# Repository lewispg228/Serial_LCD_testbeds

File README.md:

# Serial_LCD_testbeds
This repo will house testbeds for the new Serial LCDs (both versions: 16x2, 20x4)

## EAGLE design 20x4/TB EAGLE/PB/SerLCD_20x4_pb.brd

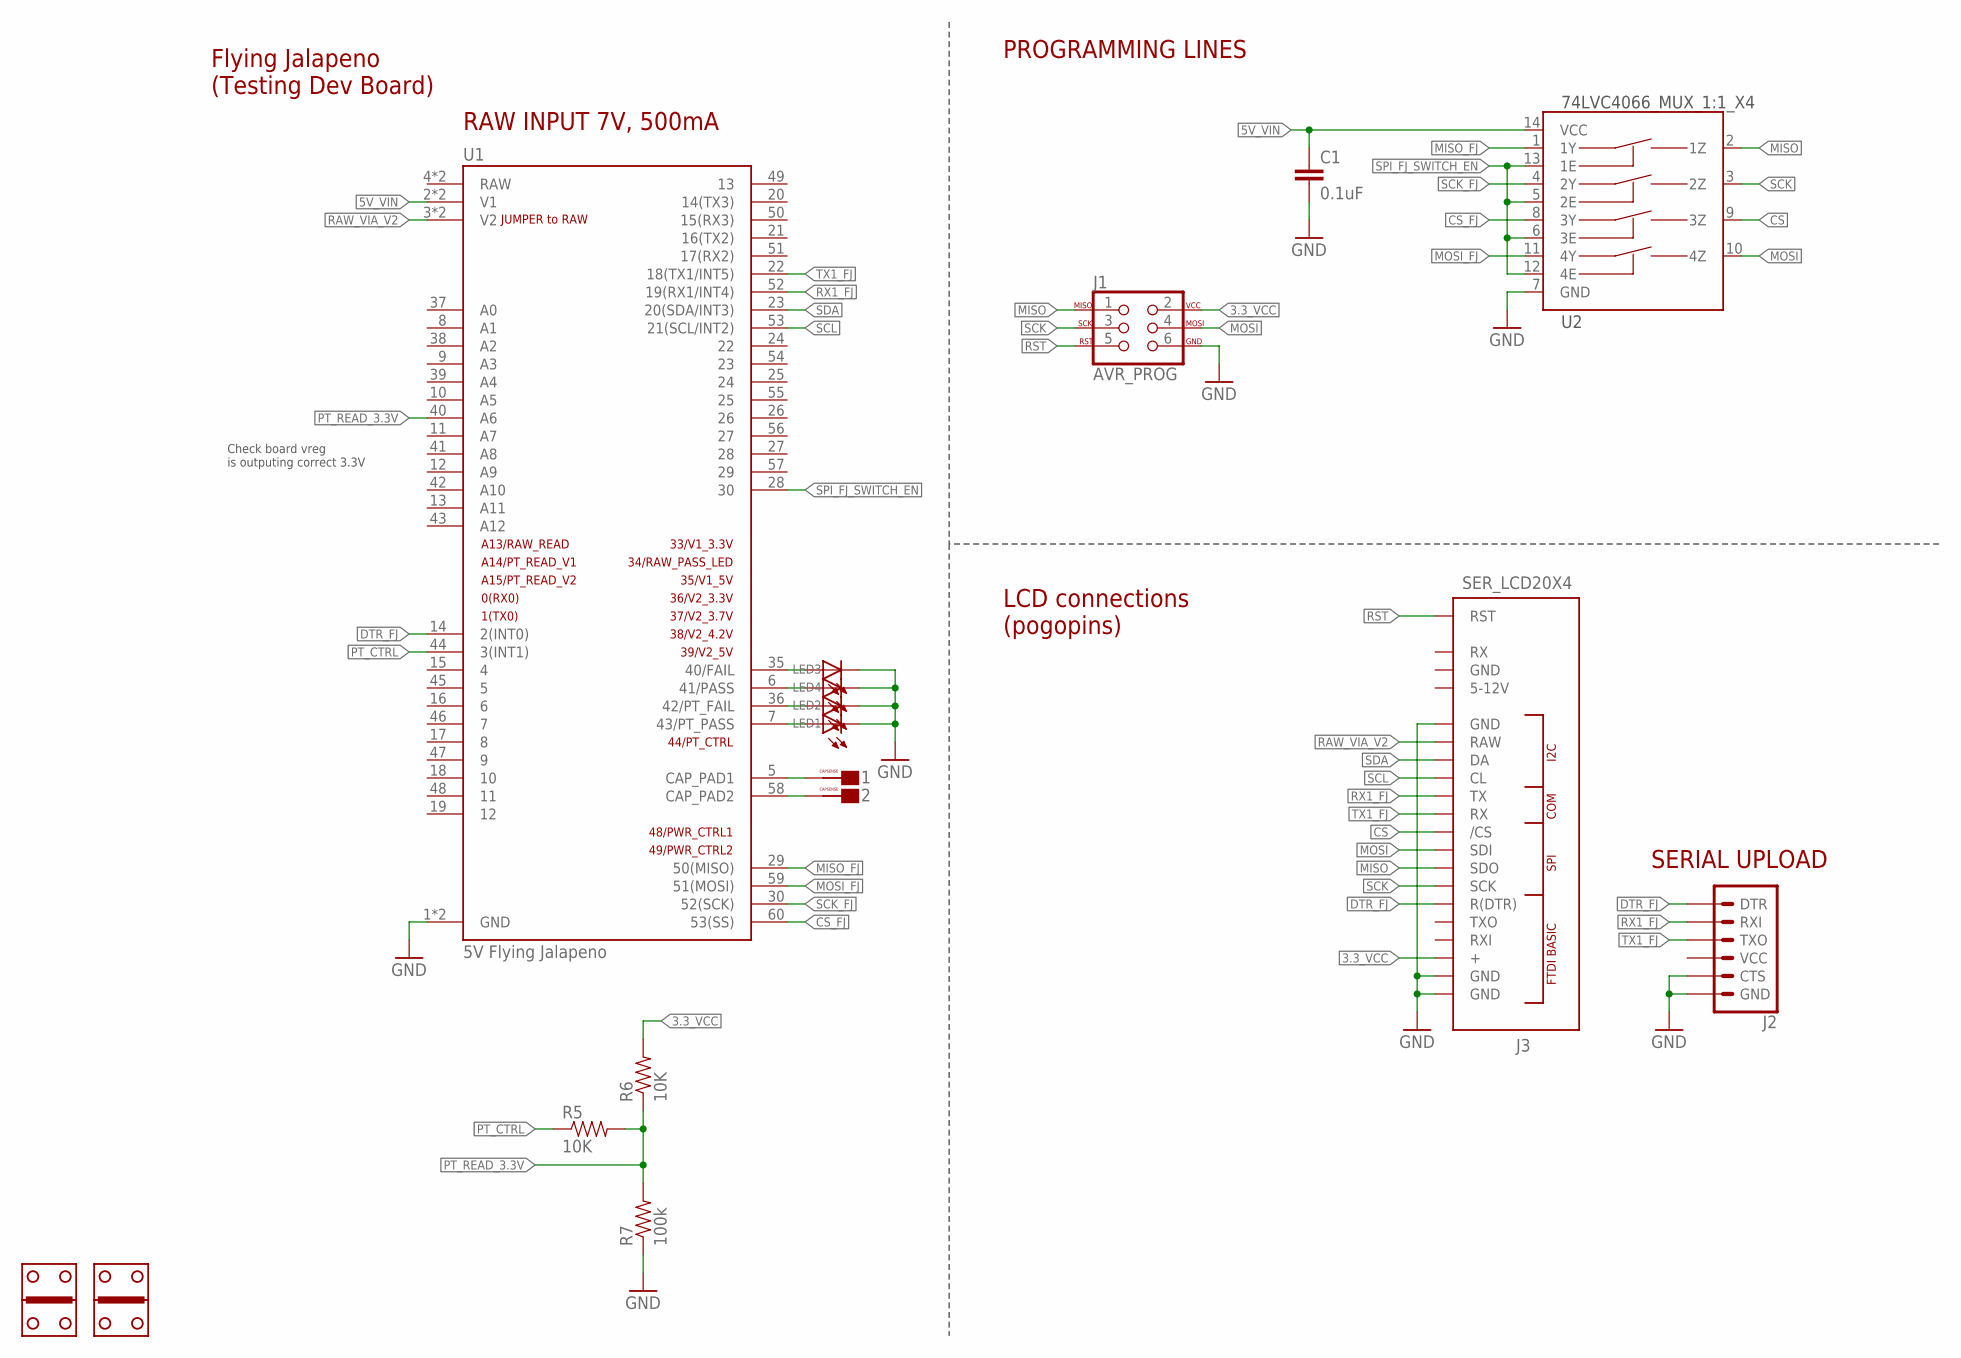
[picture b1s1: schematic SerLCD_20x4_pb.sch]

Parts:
1, 2: CAPSENSE_BUTTON_PAD_ONLY; CAPSENSE_BUTTON_PADS_ONLY
C1: 0.1uF; 0603-CAP
J1: AVR_PROG; 2X3_LOCK
J2: 6_PIN_SERIAL_TARGETLOCK; 1X06_LOCK
J3: SER_LCD20X4; SER_LCD_20X4
LED1, LED2, LED3, LED4: LED1206; LED-1206
R5, R6: 10K; 0603-RES
R7: 100k; 0603-RES
U1: 5V Flying Jalapeno; FLYING_JALAPENO_V3_1_M
U2: 74LVC4066_MUX_1:1_X4; SO14
U$6, U$7: GOLD_HINDGEPB; GOLD_HINDGE

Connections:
3.3_VCC: J1.2, J3.P$3 (+), R6.2
5V_VIN: C1.1, U1.2 (V1), U1.32 (V1), U2.14 (VCC)
CS: J3.P$10 (/CS), U2.9 (3Z)
CS_FJ: U1.60 (53(SS)), U2.8 (3Y)
DTR_FJ: J2.1 (DTR), J3.P$6 (R(DTR)), U1.14 (2(INT0))
GND: C1.2, J1.6, J2.5 (CTS), J2.6 (GND), J3.P$1 (GND), J3.P$2 (GND), J3.P$16 (GND), LED1.C, LED2.C, LED3.C, LED4.C, R7.1, U1.1 (GND), U1.31 (GND), U2.7 (GND)
MISO: J1.1, J3.P$8 (SDO), U2.2 (1Z)
MISO_FJ: U1.29 (50(MISO)), U2.1 (1Y)
MOSI: J1.4, J3.P$9 (SDI), U2.10 (4Z)
MOSI_FJ: U1.59 (51(MOSI)), U2.11 (4Y)
unnamed: 1.CAPSENSE_PAD, U1.5 (CAP_PAD1)
unnamed: 2.CAPSENSE_PAD, U1.58 (CAP_PAD2)
unnamed: LED1.A, U1.7 (43/PT_PASS)
unnamed: LED2.A, U1.36 (42/PT_FAIL)
unnamed: LED3.A, U1.35 (40/FAIL)
unnamed: LED4.A, U1.6 (41/PASS)
PT_CTRL: R5.1, U1.44 (3(INT1))
PT_READ_3.3V: R5.2, R6.1, R7.2, U1.40 (A6)
RAW_VIA_V2: J3.P$15 (RAW), U1.3 (V2), U1.33 (V2)
RST: J1.5, J3.P$20 (RST)
RX1_FJ: J2.2 (RXI), J3.P$12 (TX), U1.52 (19(RX1/INT4))
SCK: J1.3, J3.P$7 (SCK), U2.3 (2Z)
SCK_FJ: U1.30 (52(SCK)), U2.4 (2Y)
SCL: J3.P$13 (CL), U1.53 (21(SCL/INT2))
SDA: J3.P$14 (DA), U1.23 (20(SDA/INT3))
SPI_FJ_SWITCH_EN: U1.28 (30), U2.5 (2E), U2.6 (3E), U2.12 (4E), U2.13 (1E)
TX1_FJ: J2.3 (TXO), J3.P$11 (RX), U1.22 (18(TX1/INT5))

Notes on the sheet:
Check board vreg is outputing correct 3.3V
JUMPER to RAW
RAW INPUT 7V, 500mA
PROGRAMMING LINES
Flying Jalapeno (Testing Dev Board)
LCD connections (pogopins)
SERIAL UPLOAD

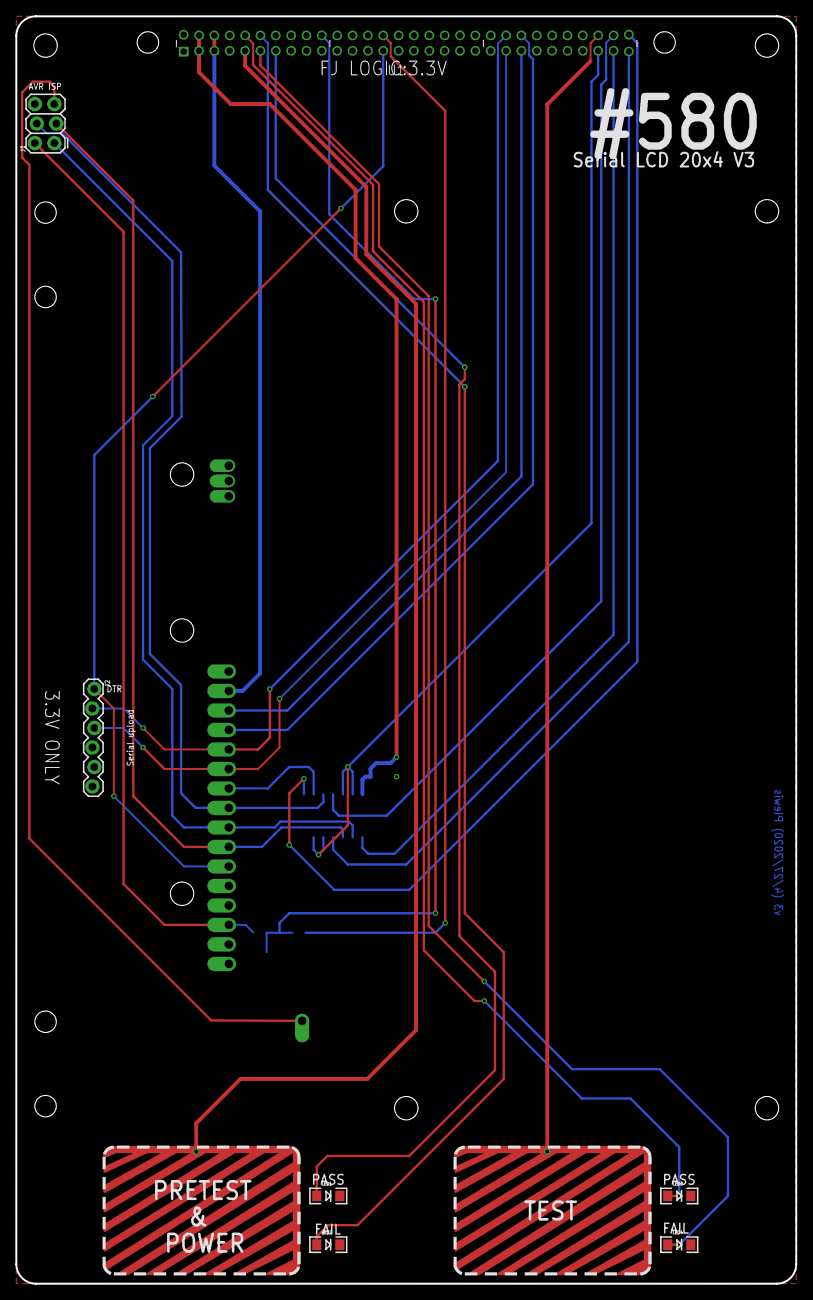
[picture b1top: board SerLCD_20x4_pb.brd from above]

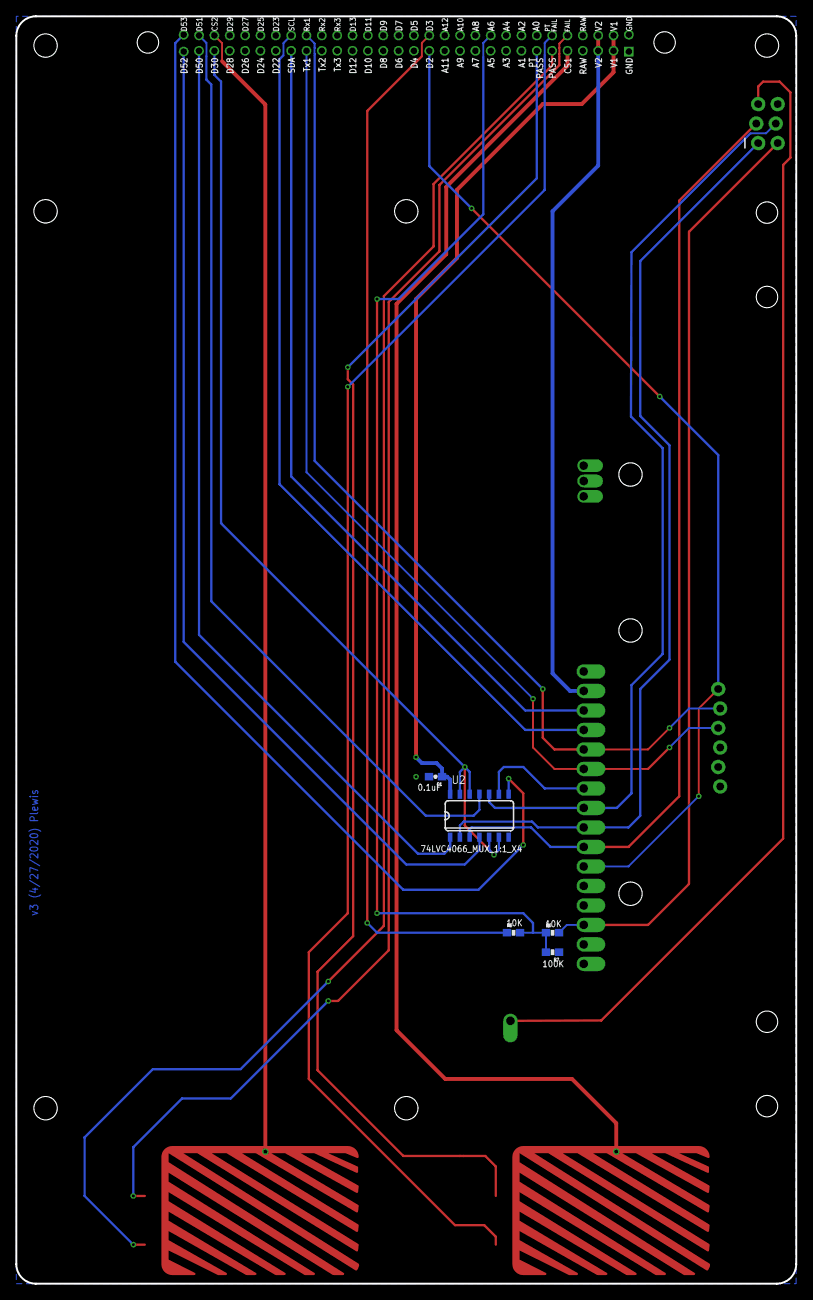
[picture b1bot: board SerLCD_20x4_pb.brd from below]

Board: 2 copper layers, 101.6 x 165.1 mm, 26 parts (5 on the bottom side), 27 nets.

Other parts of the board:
U$1, U$2, U$3, U$4, U$5, U$8, U$9, U$10, U$11: STAND-OFF-TIGHT

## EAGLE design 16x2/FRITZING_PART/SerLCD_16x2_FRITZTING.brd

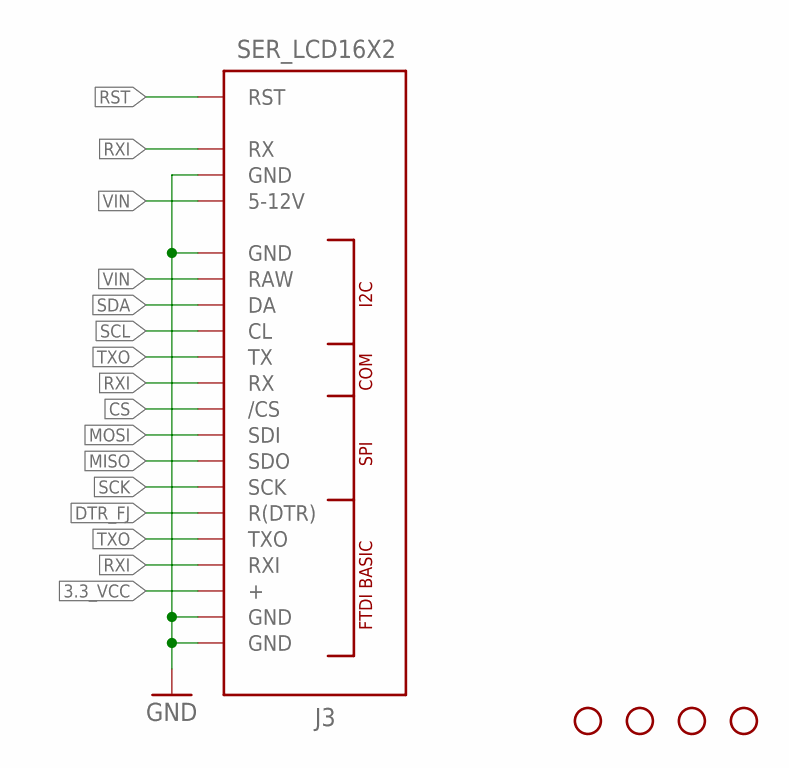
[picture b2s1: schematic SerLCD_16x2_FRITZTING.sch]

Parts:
H1, H2, H3, H4: STAND-OFF
J3: SER_LCD16X2; SER_LCD_16X2

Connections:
3.3_VCC: J3.P$3 (+)
CS: J3.P$10 (/CS)
DTR_FJ: J3.P$6 (R(DTR))
GND: J3.P$1 (GND), J3.P$2 (GND), J3.P$16 (GND), J3.P$18 (GND)
MISO: J3.P$8 (SDO)
MOSI: J3.P$9 (SDI)
RST: J3.P$20 (RST)
RXI: J3.P$4 (RXI), J3.P$11 (RX), J3.P$19 (RX)
SCK: J3.P$7 (SCK)
SCL: J3.P$13 (CL)
SDA: J3.P$14 (DA)
TXO: J3.P$5 (TXO), J3.P$12 (TX)
VIN: J3.P$15 (RAW), J3.P$17 (5-12V)

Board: 2 copper layers, 5 parts (0 on the bottom side), 4 nets, no tracks yet.

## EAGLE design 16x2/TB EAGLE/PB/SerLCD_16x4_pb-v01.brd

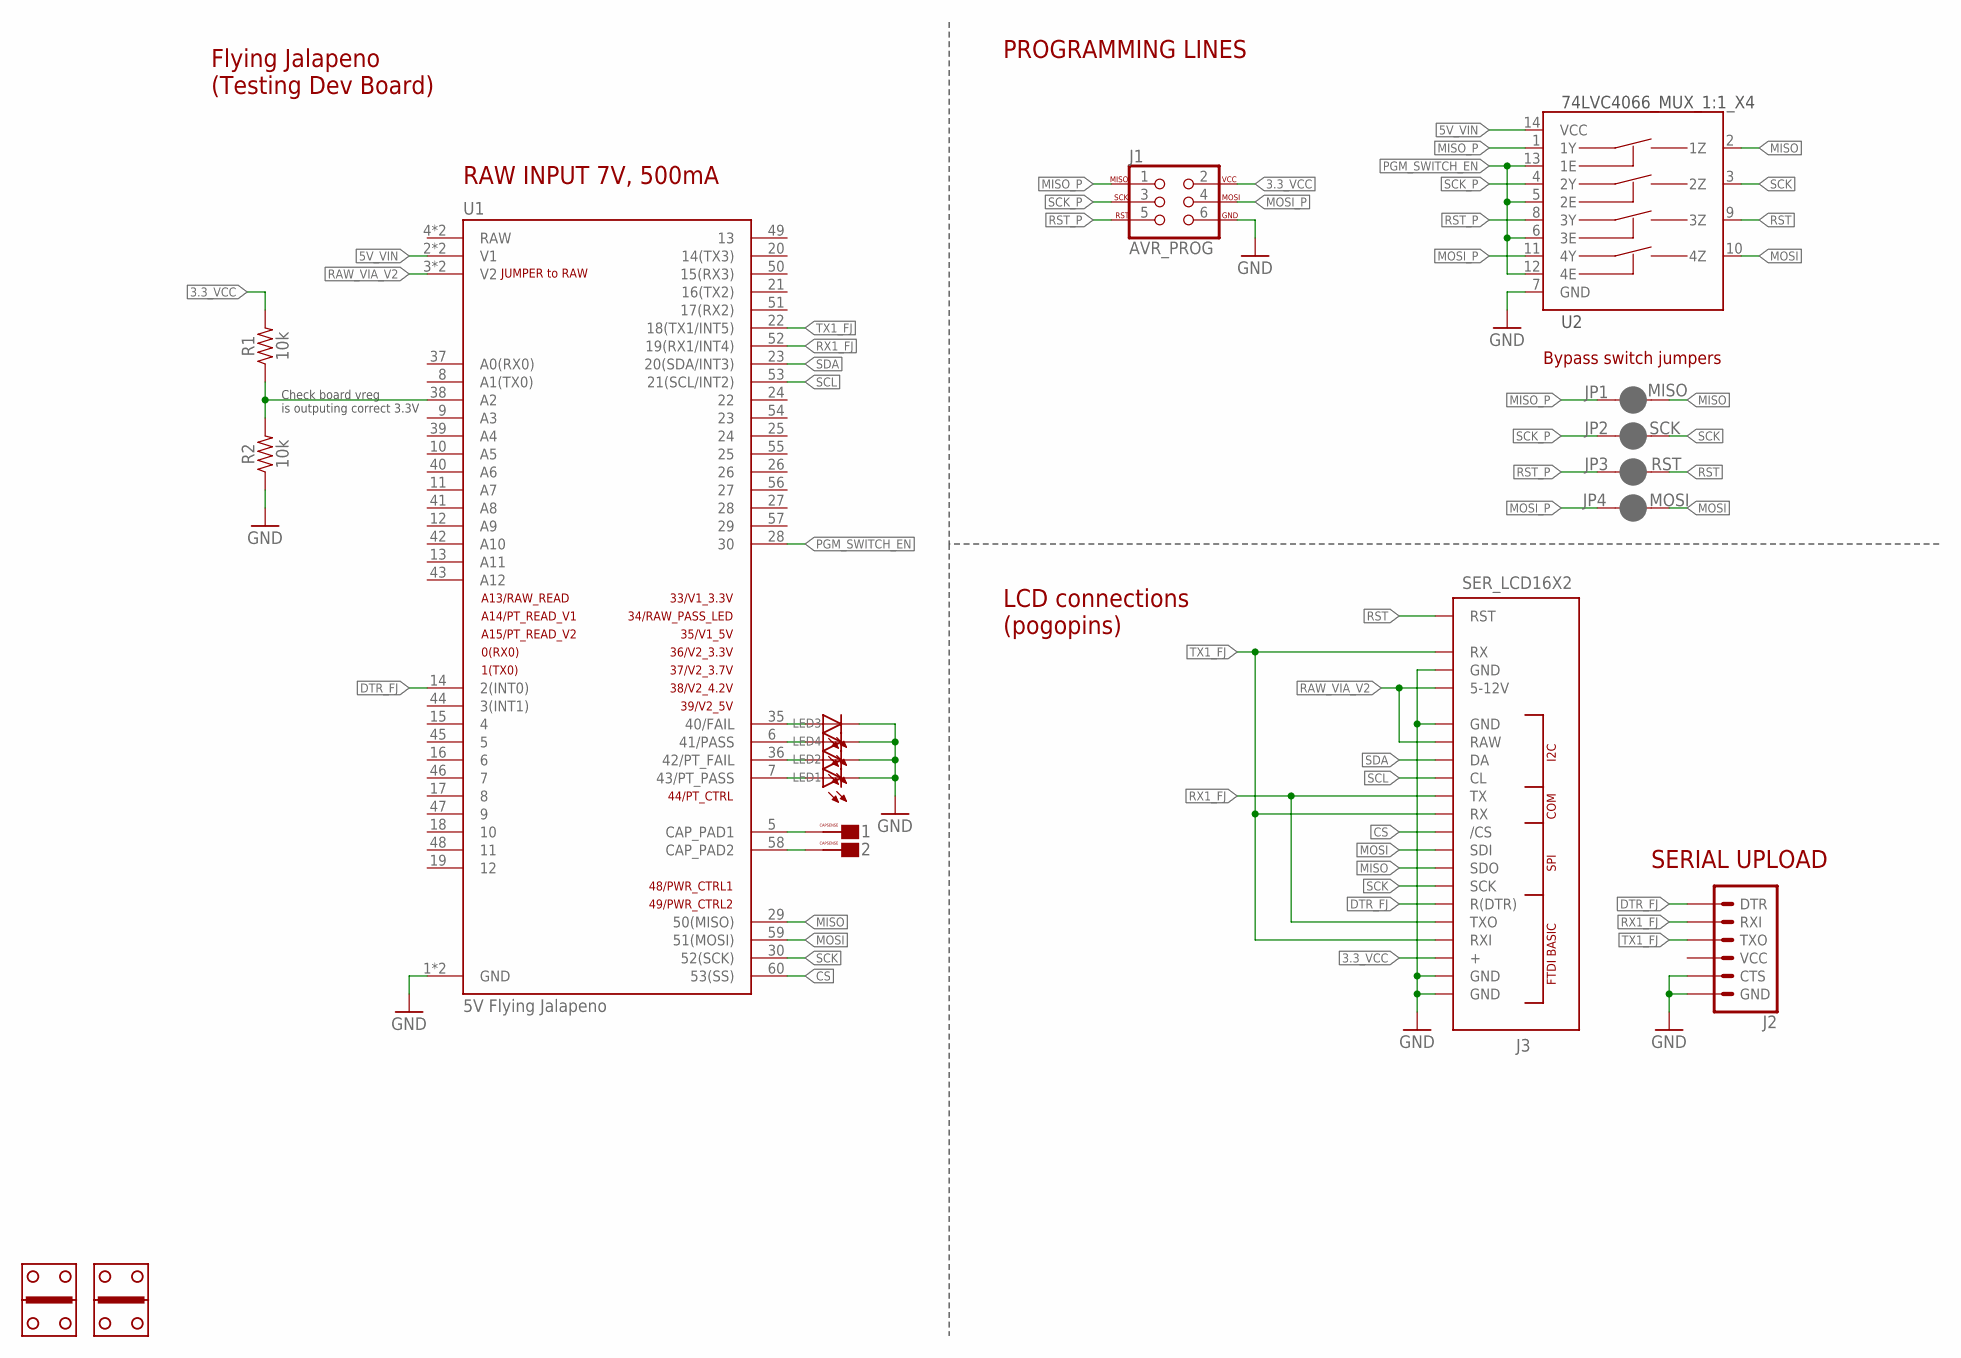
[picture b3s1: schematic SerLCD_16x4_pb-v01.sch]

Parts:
1, 2: CAPSENSE_BUTTON_PAD_ONLY; CAPSENSE_BUTTON_PADS_ONLY
J1: AVR_PROG; 2X3_LOCK
J2: 6_PIN_SERIAL_TARGETLOCK; 1X06_LOCK
J3: SER_LCD16X2; SER_LCD_16X2
JP1: MISO; SMT-JUMPER_2_NC_PASTE_NO-SILK
JP2: SCK; SMT-JUMPER_2_NC_PASTE_NO-SILK
JP3: RST; SMT-JUMPER_2_NC_PASTE_NO-SILK
JP4: MOSI; SMT-JUMPER_2_NC_PASTE_NO-SILK
LED1, LED2, LED3, LED4: LED1206; LED-1206
R1, R2: 10k; 0603
U1: 5V Flying Jalapeno; FLYING_JALAPENO_V2_M
U2: 74LVC4066_MUX_1:1_X4; SO14
U$6, U$7: GOLD_HINDGEPB; GOLD_HINDGE

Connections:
3.3_VCC: J1.2, J3.P$3 (+), R1.2
5V_VIN: U1.2 (V1), U1.32 (V1), U2.14 (VCC)
CS: J3.P$10 (/CS), U1.60 (53(SS))
DTR_FJ: J2.1 (DTR), J3.P$6 (R(DTR)), U1.14 (2(INT0))
GND: J1.6, J2.5 (CTS), J2.6 (GND), J3.P$1 (GND), J3.P$2 (GND), J3.P$16 (GND), J3.P$18 (GND), LED1.C, LED2.C, LED3.C, LED4.C, R2.1, U1.1 (GND), U1.31 (GND), U2.7 (GND)
MISO: J3.P$8 (SDO), JP1.2, U1.29 (50(MISO)), U2.2 (1Z)
MISO_P: J1.1, JP1.1, U2.1 (1Y)
MOSI: J3.P$9 (SDI), JP4.2, U1.59 (51(MOSI)), U2.10 (4Z)
MOSI_P: J1.4, JP4.1, U2.11 (4Y)
unnamed: 1.CAPSENSE_PAD, U1.5 (CAP_PAD1)
unnamed: 2.CAPSENSE_PAD, U1.58 (CAP_PAD2)
unnamed: LED1.A, U1.7 (43/PT_PASS)
unnamed: LED2.A, U1.36 (42/PT_FAIL)
unnamed: LED3.A, U1.35 (40/FAIL)
unnamed: LED4.A, U1.6 (41/PASS)
unnamed: R1.1, R2.2, U1.38 (A2)
PGM_SWITCH_EN: U1.28 (30), U2.5 (2E), U2.6 (3E), U2.12 (4E), U2.13 (1E)
RAW_VIA_V2: J3.P$15 (RAW), J3.P$17 (5-12V), U1.3 (V2), U1.33 (V2)
RST: J3.P$20 (RST), JP3.2, U2.9 (3Z)
RST_P: J1.5, JP3.1, U2.8 (3Y)
RX1_FJ: J2.2 (RXI), J3.P$5 (TXO), J3.P$12 (TX), U1.52 (19(RX1/INT4))
SCK: J3.P$7 (SCK), JP2.2, U1.30 (52(SCK)), U2.3 (2Z)
SCK_P: J1.3, JP2.1, U2.4 (2Y)
SCL: J3.P$13 (CL), U1.53 (21(SCL/INT2))
SDA: J3.P$14 (DA), U1.23 (20(SDA/INT3))
TX1_FJ: J2.3 (TXO), J3.P$4 (RXI), J3.P$11 (RX), J3.P$19 (RX), U1.22 (18(TX1/INT5))

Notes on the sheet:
Check board vreg is outputing correct 3.3V
JUMPER to RAW
RAW INPUT 7V, 500mA
Bypass switch jumpers
PROGRAMMING LINES
Flying Jalapeno (Testing Dev Board)
LCD connections (pogopins)
SERIAL UPLOAD

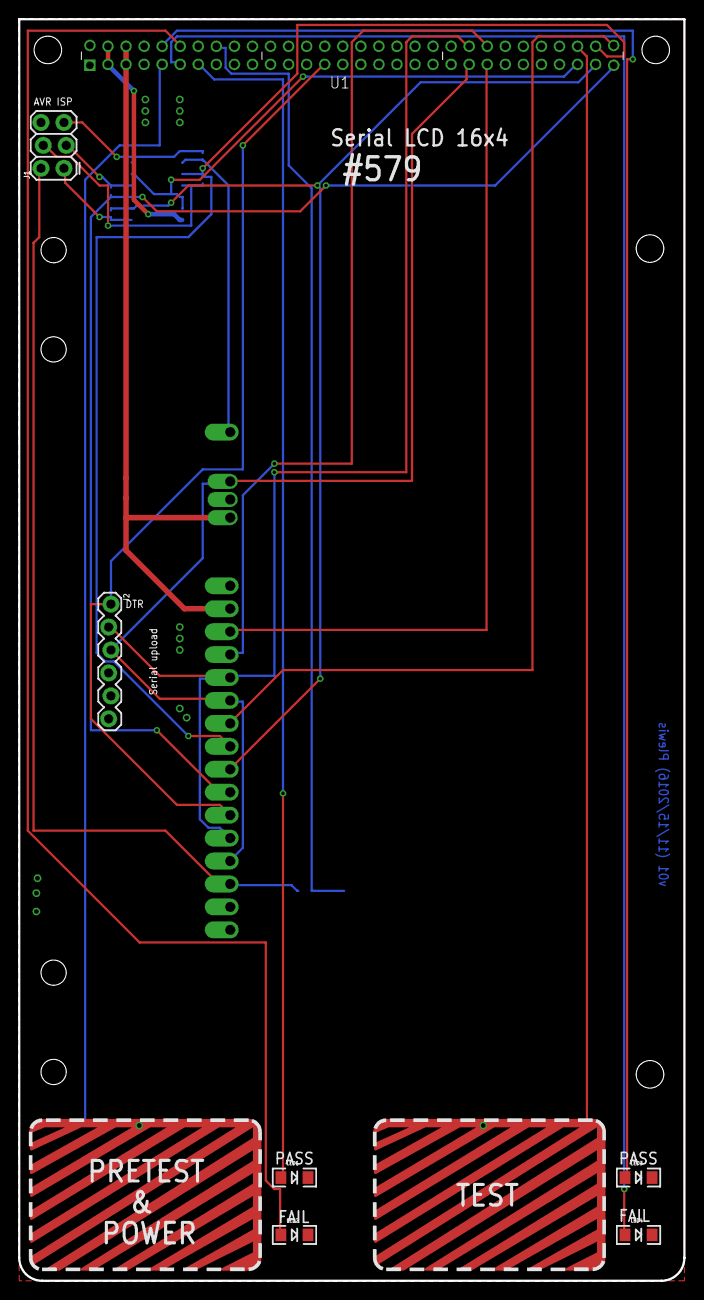
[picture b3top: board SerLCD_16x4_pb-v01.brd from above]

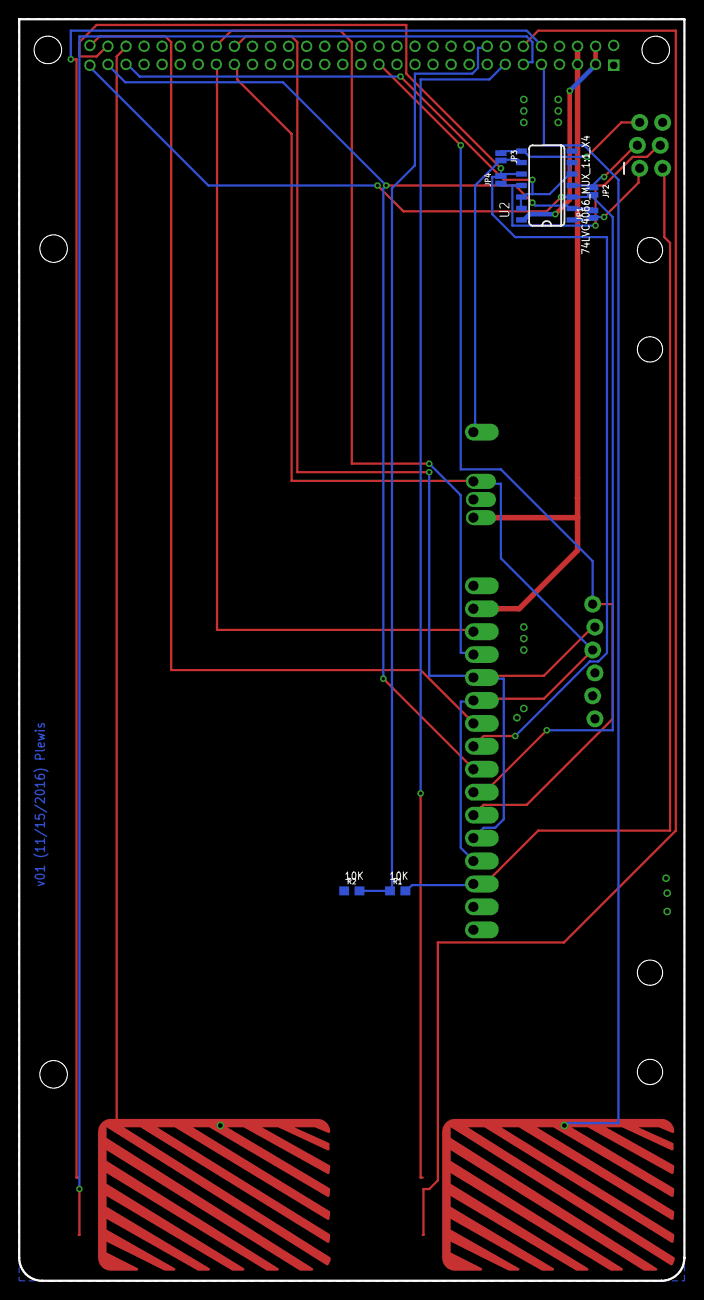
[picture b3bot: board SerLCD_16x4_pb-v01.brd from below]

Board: 2 copper layers, 73.7 x 139.7 mm, 21 parts (7 on the bottom side), 26 nets.

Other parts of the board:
U$3, U$8: STAND-OFF-TIGHT

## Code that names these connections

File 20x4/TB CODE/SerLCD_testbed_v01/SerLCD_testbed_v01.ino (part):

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* 
*/
#define STATUS_LED 13
#define PGM_SWITCH_EN 30
#define PT_CTRL_PIN 3
#define PT_READ_PIN A6
#define DTR_FJ 2
#define CS_PIN 53

// Display size. The same testbed code goes onto both versions of the testing hardware,
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void setup()
{
  pinMode(STATUS_LED, OUTPUT);
  pinMode(PT_CTRL_PIN, OUTPUT);
  digitalWrite(PT_CTRL_PIN, LOW);

  pinMode(DTR_FJ, INPUT);
  pinMode(18, INPUT); // TX1, connected to RXI on product
  pinMode(19, INPUT); // RX1, connected to TXO on product
  

  FJ.enablePCA(); //Enable the I2C buffer
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      //Check v2 for shorts to ground. Note, V1 is being used to power the switching programming lines IC
      // also a third pretest for 3.3V output
      boolean PT_VIN = FJ.powerTest(2);
      boolean PT_33V = FJ.PreTest_Custom(PT_CTRL_PIN, PT_READ_PIN);
      if (PT_VIN == true && PT_33V == true)
      {
        FJ.setV2(true, 5); // note, this is connected to RAW source via jumper on FJ

        // supply 5V to programming lines swittcher IC. Note, this is the only portion of the tested using this power supply, so we can just leave it on 100% of the time.
        FJ.setV1(true, 3.3); //Turn on power supply 1 to 3.3V
        pinMode(PGM_SWITCH_EN, OUTPUT);
        digitalWrite(PGM_SWITCH_EN, HIGH); // enable switch for initial programming. We will want to disable this when we move to other testing.

        Serial.println("Pre-test PASS, powering up...\n\r");
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    FJ.dot();

    digitalWrite(PGM_SWITCH_EN, LOW); // DISable switch for programming.
    pinMode(PGM_SWITCH_EN, INPUT);

    failures = 0; // reset for testing a second time

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  Serial.println("testing 3.3V output on board VCC");

  // THIS IS SPLIT WITH A PRETEST CIRCUIT
  // This means that we need to write the PT_CTRL pin LOW, in order to get a split "closer" to 50%.
  pinMode(PT_CTRL_PIN, OUTPUT);
  digitalWrite(PT_CTRL_PIN, LOW);
    
  //pin = pin to test
  //correct_val = what we expect.
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  FJ.disableRegulator2();

  digitalWrite(PGM_SWITCH_EN, LOW); // DISable switch for programming.
  pinMode(PGM_SWITCH_EN, INPUT);
  
  targetPowered = false;

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
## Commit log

2016-11-14 added gitignore
    standard SFE
2016-11-15 prelim layout and temp library for dimensions
2016-11-15 finished up devices in temp library
2016-11-15 Some library work, and the 16x4 is almost done
2016-11-15 labels on prgramming headers
2016-11-15 high level written test plan (no pics yet)
2016-11-15 PM and REF ONLY packages
    16x4 only. these will help with designing upper layers of pogobed (PM,
    PF, WT)
2016-11-15 finished up 16x4 (PB/PM/PF/WT)
2016-11-15 finshed up 20x4, RFR
2016-11-15 added backlight verify to documentation
2016-12-06 added preTest to 3.3V on 16x2
    This will also be used to verify that the vreg is outputing proper
    voltage later in the test.
    NOTE: I still need to add this to 20x4 version
2016-12-06 added preTest to 3.3V output on 20x4
    ready to order both designs... gonna throw on a QC panel asap
2016-12-06 added rout out area to PM
2016-12-06 added "route out" text to PF
2017-02-20 Arduino compatible bootloader for 11.0592MHz
    pulled this in from bug attachment from nate on 1/11/2917
2017-02-21 preliminary testbed code for 20x4
    pretests working. powers up, sets contrast to 50, sends full screen of
    numbers over serial.
    Still need to incorporate all other comm lines to product, and
    backlight.
2017-02-21 Testing plan in comment at top
2017-02-21 comments on initial serial test
2017-02-21 moved serial test into function added i2c_ping
    also moved "test_vcc()" into "test()"
2017-02-21 serial, spi, i2c working
    still need backlight, and "all characters full" test.
    Also, might be able to somehow use same code on both testbeds, but not
    sure if this is possible.
2017-02-21 backlight test - wonky on the monochrome
    I think it's wonky because I am sending it RGB commands and it's
    monochrom 20x4 I'm testing with right now.
2017-02-22 combined hex - boot and firmware
    note, I also chopped out the unnecessary blank space in the hex file.
2017-02-22 created monochrome and RGB backlight test
    This will be less confusing for the techs. I will call the appropriate
    function for the type of screen...
    not sure what to do about the 16x4 though.: both the RGB and monochrome
    version of that share a testbed, so they will probably have some
    confusing messages pop up if the screen is monochrome, but I still send
    commands for RGB.
2017-02-22 fixed power down issue
    It seems that the CS_PIN is "slightly" jumpered to my high side switch
    control lines (I'm thinking this is a fault in the FJ itself or the
    daughter board).
    I'm measuring 40 ohms between CS_PIN and 49/48.
2017-03-27 Moving VCC test to 3.3V
    3.3V because that's the logic level of the latest proto I'm working
    with. All future 20x4 lcd screens should have a logic of 3.3V
    Note the board in hand right now has a sticker with a date on it that
    says "2016-9-25"
2017-04-03 still deving for the 20x4
    VCC test actually is reading more like 1.7V
    movign to the RGB backlight test - to see all three colors
    removed contrast test - found that 10 works well.
    slowed down delays a bit to see whats going on
2017-04-03 removed contrast test
2017-05-15 added var to set_contrast(), also changed backlight testing
2017-05-15 programming lines switch IC vcc to 3.3V
    Also, some rx tx testing on prototypes.
2017-05-15 Adding in VCC to correct verifyVoltage() when using 3.3V logic FJ
    Note, also had to update FlyingJalapeno library repo
2017-05-15 got RGB backlight up fades working
2017-05-16 updating FJ setup comment to be accurate
    All of the LCDs operate at 3.3V, so we match that with the FJ on it's
    own VCC and the V1 that supplies logic level for the programming lines
    switch.
2017-05-19 protective bases
    designed by measuring from actual built up testbeds. worked out pretty good, but would have been much faster to convert from eagle.
    Note, there is a file that contains both 16x2 and 20x4, for easier laser cutting.
2017-10-13 desplay size defines and some manual rgb control for testing
2017-11-21 removing "backlight_test_loop()" slowing down testing
    Going back to "production style" testing, which means I am remvoing the
    loop waiting for manual control characters.
    I also changed the upfades timing to 3 seconds, to slow it down for a
    video I made for amotech.
2018-06-07 Prepped 16x4_PM for acrylic - drills to 55mils
    also moved "route out" text to tplace
    also created dxf file for lazering
2018-06-18 speeding up test for amotech production
    decreased a lot of delays, also added in some delays (just 200ms) to break up the sections of the test. Without these little delays, it seemed to be missing the I2C and SPI commands.
2018-06-18 exporting combined hex for 20x4
2018-06-18 combined hexes for both versions of testbeds (16x2 and 20x4)
    Put them in a zip for emailing
2018-06-18 moving combined hex files into proper folder
2018-06-19 created a simple board file for fritzing part creation hope it works
2018-10-10 exported to dxf for lazering acrylic layers
2019-02-18 updating switch circuit and re-routing
    the pi_grammer has the isolation switch, so I am now using the onboard switch to isolate the FJ's SPI lines. This will hopefully elliminate the need for the occasional hard reset on the testbed.
    Re-routing everything manually. The original design was autorouted and was pretty ugly.
    Currently most of the important stuff is routed nicely. Still needs LEDs and some switch stuff routed.
2019-02-19 finished re-routing on PB
2019-02-21 renaming without version number in name
2019-02-21 20x4 pb routing done
    -changed switch to isolate FJ SPI lines (because the new pi_grammer has isolation built in)
    -added more support beam standoffs
    -moved to new FJ footprint for easier assembly on RA 2x30 header.
2020-04-27 16x2 testbed PB updated for new qwiic connector version
2020-04-27 20x4 testbed PB updated for new qwiic connector version
    -also removed old PM footprints, cuz these aren't used in making acrylic layers anyways, and they are now out of date with pogopin spacing.

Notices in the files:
parts and their libraries:
SparkFun-Hardware: Licensing: Creative Commons ShareAlike 4.0 International - https://creativecommons.org/licenses/by-sa/4.0
